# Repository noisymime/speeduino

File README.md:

<div align="center">

##### A low cost, DIY friendly Engine Management System (ECU) based on the Arduino framework
</div>

## Speeduino
The Speeduino project is a flexible, fully featured Engine Management Systems (EMS aka ECU) based on the low cost and open source Arduino platform. It provides the hardware, firmware and software components that make up an engine management system, all provided under open licenses. With over 1000 installations, Speeduino has matured into a product that meets the needs of the hobbyist and enthusiast community without driving prices to the levels of traditional aftermarket ECUs.

## Documentation
The Speeduino online manual can be found at: https://wiki.speeduino.com

## Where to Buy
[Pre-made Speeduino units/boards are available from a number of official resellers](https://speeduino.com/home/where-to-buy)

These resellers all contribute a portion of sales back to the project to allow for continued development to take place and we encourage sales through them whenever possible. 
 
Of course, being open source, you are free to use the design files provided here to create your own hardware! 

## Support
In addition the manual referenced above, Speeduino has a large and very vibrant community of people to help out with your setup or any questions you might add. 

* [Speeduino Forum](https://speeduino.com/forum) 
* [Discord](https://discord.gg/YWCEexaNDe)
* [Facebook](https://www.facebook.com/groups/191918764521976/)

## Contributors

This project exists thanks to all the people who contribute, both in terms of code and testing provided. If you'd like to get involved, please have a read through [Contributing](contributing.md) and then jump on Discord to discuss things further

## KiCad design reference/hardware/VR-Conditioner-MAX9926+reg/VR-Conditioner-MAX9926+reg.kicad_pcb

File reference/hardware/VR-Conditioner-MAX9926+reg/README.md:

I hope this helps anyone interested.
Anyway, I've done what I can & it's now ready for many eye-balls.

Phill

### 2021-02-23
I have not made & tested this design but it is barely changed from the manufacrurers data sheets or other designs.
If you make & test it then please advise.

I'm new to KiCAD so I don't know how to do some things.  Such as how to have an 8-pin set of holes without a 3D chip sitting in it.
Or how to do an 8-pin header in the shape & pin count order of a chip.

### 2021-02-24
Changed version number to 3.5 so that it reflects relative cronology from previous design.
Renamed this from Notes.txt to README.md & corrected the date above.
Added Comments to schematic, inc. single-sided design allowing 'Letter' postage!
Updated BOM in schematic to reflect readily available parts found on OctoPart.

### 2021-04-22
Goal: give the left 6 passive components some space from the edge.
Re-route COUT1 from DIP.8 to SIL.4 in green so no signal traces are by the edge.
Shift right 5 components slightly right
Shift DIP, chip & hidden cap slightly right
Shift left 6 components slightly right
Re-route left 6 components to avoid side swapping, keeping the larger SMTs.
Ensure GNG plane encircles everything with a via in each corner.
Ensure all 'thin' traces are 0.20mm (up from 0.16)
Tidy with some symetry.

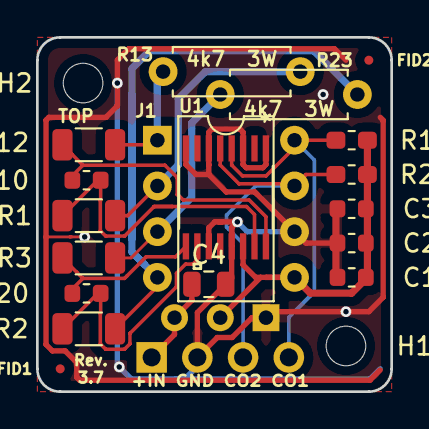
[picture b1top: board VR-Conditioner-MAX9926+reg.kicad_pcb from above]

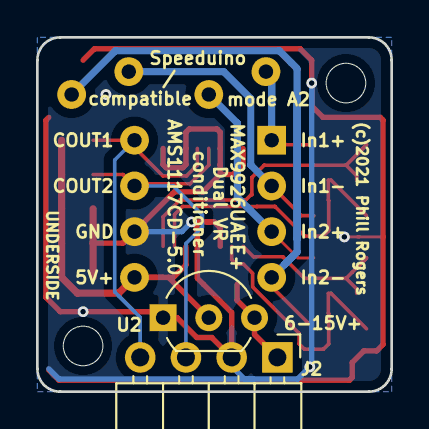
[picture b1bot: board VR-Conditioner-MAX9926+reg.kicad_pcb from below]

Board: 2 copper layers, 19.7 x 19.7 mm, 22 parts (2 on the bottom side), 13 nets.

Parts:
C1: 10n; C_0603_1608Metric
C2: 100n; C_0603_1608Metric
C3: 1u; C_0603_1608Metric
C4: 10u; C_0805_2012Metric
C10, C20: 1n; C_0603_1608Metric
FID1, FID2: Fiducial; Fiducial_0.5mm_Mask1mm
H1, H2: MountingHole; MountingHole_2.2mm_M2
J1: 8-pin header; DIP-8_W7.62mm
J2: Edge; PinHeader_1x04_P2.54mm_Horizontal
R1, R2, R3, R12: 10k; R_1206_3216Metric
R10, R20: 1k; R_0603_1608Metric_Pad1.05x0.95mm_HandSolder
R13, R23: 4.7k; R_Axial_DIN0207_L6.3mm_D2.5mm_P7.62mm_Horizontal
U1: MAX9926UAEE+; MAX9926UAEE&plus_
U2: AMS1117CD-5.0; TO-92_Inline_Wide

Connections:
+12V: C4.1, J2.1, U2.3
/COUT1: J1.8, J2.4, R10.2, U1.4
/COUT2: J1.7, J2.3, R20.2, U1.5
GND: C1.2, C2.2, C3.2, C4.2, J1.6, J2.2, U1.1, U1.3, U1.6, U1.8, U1.11, U1.13, U2.1
unnamed: C10.1, R12.1, U1.16
unnamed: C10.2, R1.1, U1.15
unnamed: C20.1, R2.1, U1.10
unnamed: C20.2, R3.1, U1.9
unnamed: J1.1, R12.2, R13.1
unnamed: J1.2, R1.2, R13.2
unnamed: J1.3, R3.2, R23.1
unnamed: J1.4, R2.2, R23.2
VCC: C1.1, C2.1, C3.1, J1.5, R10.1, R20.1, U1.14, U2.2

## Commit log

2022-01-07 boostLoadMax addition
2022-01-09 IAC IAT PWM Addition
    IAC IAT PWM Addition
2022-08-16 iacIATPWM
2022-08-16 typo fix
2024-02-08 Add unit tests for triggerSetEndTeeth_SuzukiK6A
2024-02-08 Bug fix - use correct parameter when calling stdGetRPM
2024-02-08 Compute triggerToothAngle from the fixed tooth angle array.
2024-02-08 triggerSetEndTeeth_SuzukiK6A - hoist duplicated code into calcEndTeeth_SuzukiK6A (like we did for some other decoders).
2024-02-09 MISRA fixes for Suzuki K6A decoder
2024-02-24 Bug fix - consistent #ifdef (ANALOG_ISR/ANALOG_ISR_MAP) Also replace multiple #ifdefs with inline function.
2024-02-24 Conditional compile to allow MAP sensor read pin even when using analog ISR Useful for development testing
2024-02-24 MISRA fixes for sensor.cpp
2024-02-25 Remove mapErrorCount - it's unused (only ever written to, never read)
2024-02-25 Replace duplicate filter macros with one inline function: LOW_PASS_FILTER (which is MISRA compliant).
2024-02-25 Remove unused global variables statuses::batADC fpPrimed - duplicate of statuses::fpPrimed injPrimed - duplicate of statuses::injPrimed
2024-02-25 Encapsulate MAP variables
2024-02-25 Deduplicate MAP reading code
2024-02-26 Split out definition of statuses struct. Break circular header dependencies.
2024-02-26 Separate out getLoad() function
2024-02-26 Bug Fix: getAdvance1() & getAdvance2() should return a signed value.
2024-02-26 secondarytables.cpp - extract duplicate code into functions.
2024-02-26 Bug fix: BIT_STATUS3_FUEL2_ACTIVE not set in 2 cases.
2024-02-26 Performance: secondaryTables call percentage() (which is optimised)
2024-02-26 Add secondary table tests
2024-02-26 Bug Fix: do not correct secondary spark multiplier
2024-02-26 Unit test no secondary spark with fixed timing.
2024-03-09 Make readBaro() independent of instanteneousMAPReading() Removes a conditional and reduces module surafce area
2024-03-09 Add isEngineRunning() to capture duplicate code
2024-03-09 Force loop() inline Reduces stack usage.
2024-03-09 Use structs to capture the MAP algorithm state. Also apply ATOMIC_BLOCK to prevent tearing of ISR modified variables.
2024-03-09 Remove validateMAP() - since we validate every sensor reading, it wasn't doing anything.
2024-03-09 Use 16-bit comparisons
2024-03-19 Use common setScheduleNext function.
2024-03-19 Initialize all Schedule members in constructor
2024-03-19 Extract common schedule state into Schedule
2024-03-19 Schedules: remove endCompare We had 2 paths to set the inj/ign end comparator: using duration; or using endCompare Replace with Duration - in timer ticks (since it's a smaller data type)
    Saves memory & simplifies code.
2024-03-19 Remove Schedule::hasNextSchedule Use a flag value in nextDuration instead.
2024-03-19 Remove Schedule.startCompare It is only used within the set*ScheduleRunning() functions as an intermediate calculation variable.
2024-03-19 Start the schedule timers externally And never turn them off - they were pretty much on continuosuly anyway.
    Saves 36 bytes
2024-03-19 Scheduler callbacks are set in pairs So model that with a setCallbacks() function.
2024-03-19 Rename FuelSchedule members to match IgnitionSchedule
2024-03-19 Schedulers - remove inline_always: let the compiler decide.
2024-03-19 Consolidate timeout calculation
2024-03-19 MISRA fixes
2024-03-19 Save RAM: drop Schedule::durationNext - use new Status setting + existing Duration instead.
2024-03-19 Use macros to define schedule ISRs (removes repeated code)
2024-03-19 Use a state machine idiom to consolidate timer ISR code.
2024-03-21 use latest available codespell dictionaries
2024-03-21 add codespell CI action
2024-03-21 Working decoder 36-2-1 with wasted spark
    - Formated decoders source file => Fixed a closing bracked for
    triggerPri_ThirtySixMinus21
    - triggerSetEndTeeth_ThirtySixMinus21 actually calls
    triggerSetEndTeeth_missingTooth (no need to duplicate code)
    - Changed the teeth numbering on the trigger wheel. Now tooth #1
    is at TDC piston #1. This fixed a bug where the algo would never
2024-03-22 Add optimized 32-bit shifting
2024-03-22 Tooth based time to angle coversion is only used by a few decoders. So move the functions into decoders.cpp
2024-03-22 Better separation of deocders and crank maths.
2024-03-22 Apply optimised shifts
2024-03-22 Doxygen
2024-03-23 Split out PW calcs to separate .H & .CPP
2024-03-23 Chain PW intermediate calcs Use size integer types
2024-03-23 Refactor: extract computePwLimit()
2024-03-23 Optimize PW
2024-03-23 inline getVE1 & getAdvance1
2024-03-23 Optimize computePwLimit() for nSquirts==1
2024-03-23 Use libdivide to calculate pulse width limit
2024-03-23 Added pwApplyNitrous() - step 1 in cleanup.
2024-03-23 Add nitrous inside PW()
2024-03-23 Move staging PW calc into single PW calculation. This makes it unit testable.
2024-03-23 Initialize req_fuel_uS where it's declared I.e. in pw_calcs.cpp
2024-03-23 Encapsulate primary & secondary fuel stages
2024-03-23 Encapsulate inj_opentime_uS: Save memory - doesn't need to be global Pulse widths will be zero if not valid: Faster comparisons
2024-03-23 Bug fixes
2024-03-25 Remove libdivide: optimise powers of 2 only. Slightly faster & saves 3 bytes
2024-03-25 Tiny perf improvement: compile time correction shifts
2024-03-27 Extract percentApprox from PW calculations, optimize and unit test..
2024-03-27 Pulse width calcs: flatten & force inline
2024-03-27 Add PW unit tests
2024-03-27 pwApplyNitrousStage() now uses Arduino map() function.
2024-04-08 boostControlMAPLoad
2024-04-08 iacIATPWM
    commit fc3e581bc3a3aaab6b5e040dba0a6eb231683d04
    Author: shiznit304 <62686180+shiznit304@users.noreply.github.com>
    Date: Sun Apr 7 21:21:31 2024 -0500
    iacIATPWM
2024-05-30 Unit test calculateRequiredFuel
2024-05-30 Unit test correctionFloodClear
2024-05-30 Make TPS AE tests independent
2024-05-30 Unit test correctionASE
2024-05-30 Add test_maths_div10_s16_perf
2024-05-30 Use RUN_TEST_P to reduce test RAM usage
2024-05-30 Add unit tests for correctionCranking
2024-05-30 Add test_corrections_MAE
2024-05-30 Add unit tests for correctionLaunch
2024-05-30 Unit test flex & fuel temp corrections, plus minor cleanup
2024-05-30 Test repetability - initialiseAll at the start of every test
2024-05-30 Unit test battery correction
2024-05-30 Unit tests - avoid forward declarations
2024-06-09 Convert MISRA script to Powershell
2024-06-09 Script was returning all errors, not just the error count (as intended)
2024-06-10 Separate out populate_table() from 3D table tests
2024-06-10 Separate calculation of AFR target from correction (and unit test the calculation). Separation of concerns and will make unit test AFR correction easier.
2024-06-10 Unit test correctionsFuel
2024-06-10 Unit test correctionAFRClosedLoop
2024-06-10 Unit test all ignition corrections
2024-06-10 DFCO - test behavior not implementation
2024-06-10 Add populate_2dtable_P test utility function
2024-06-10 Shrink unit test for faster build/upload/execute We just need the 2D tables wired up, not the whole system initialized. 1. Factor out construct2dTables() from initialiseAll() 2. In the unit tests, ca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
2024-06-10 Tweak tests to pass on Teensy 3.5
2024-06-10 Add compile time buffer overflow check to RUN_TEST_P
2024-06-10 Add test_correctionsDwell_uses_batvcorrection
2024-06-10 Add AE test assertion: especially for MAE
2024-06-10 Use TEST_ASSERT_BIT_[HIGH_LOW] instead of TEST_ASSERT_[TRUE|FALSE] Better failure messages, declares intent
2024-06-10 Add AE timeout unit tests
2024-06-10 Igniton corrction test: expand assertions: make sure all corrections test both positive an negative advance values.
2024-06-10 Convert copy/paste 2D table construction code into shared functions
2024-06-13 Add PS help
2024-06-15 More detailed debug output
2024-06-21 uS_TO_TIMER_COMPARE should return COMPARE_TYPE
2024-06-21 Break *circular* header dependencies: globals.h -> board_avr2560.h -> globals.h
    1. Move board header selection into board_selector.h
    2. Remove BOARD_H - board_selector.h should include the correct header
    3. Put board specific definitions in the board specific header files.
2024-06-21 MISRA fixes
    Remove coil toggle functionality: it's unused and probably a really bad idea to use it anyway (risk of accidental overdwell).
    Remove mc33810_[1|2]_returnState: unused.
2024-06-21 ARM cores call moveToNextState directly
2024-06-21 Move scheduler AVR interrupt setup into board_avr2560.cpp (why should AVR board setup differ from the other boards?)
2024-08-02 removed unsupported/unused STM32F103 references
2024-08-03 Generate table read/write functions This means we can stop using the void* based functions from pages.*. Better type safety.
2024-08-03 doUpdates() doesn't need to/shoudn't use page iteration.
2024-08-03 Remove unused table type (table3d8RpmTps)
2024-08-03 Split out definition of statuses & config page structs. Break circular header dependencies.
2024-08-03 Move resetConfigPages(), rename setTuneToEmpty() This function is unrelated to storage.

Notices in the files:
README.md:
License: GPLv3
reference/hardware/VR-Conditioner-MAX9926+reg/VR-Conditioner-MAX9926+reg.kicad_pcb:
(c)2021 Phill Rogers @ TechColab.co.je
parts and their libraries:
Copyright 2016 Accelerated Designs. All rights reserved.
